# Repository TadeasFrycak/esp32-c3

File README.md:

# ESP32-C3 Nano

:warning: **Temporary warning**: This version of PCB has not been yet validated and it is actively being worked on

Compact and minimalist **ESP32-C3** breakout designed in [KiCAD](https://www.kicad.org/)

## Features
- **Breadboard friendly**
- **Compact dimensions** - 46 x 21.5 mm
- **USB-C** connector for programming (using CDC, so no external usb-serial convertor)
- **External VIN pin** with schottky diode (so both VIN and USB power can be applied at the same time)
- **Low dropout regulator to 3V3** (LDO)
- **Reset** and **Boot** buttons on board
- **Integrated PCB antenna**
- **USB ESD protection**
- Chip: **ESP32-C3FH4**

## Interactive HTML BOM
Thanks to the awesome KiCAD [IBOM](https://github.com/openscopeproject/InteractiveHtmlBom) plugin, we can now generate this stunning BOM! You can find it in docs/ibom.html

## Schematics

## Contributors:
- **SZKANDERA Filip** (filip.szkandera@gmail.com, [@FilipSzkandera](https://github.com/FilipSzkandera/))
- **FRYČÁK Tadeáš** (info@frycak.com, [@TadeasFrycak](https://github.com/TadeasFrycak/))

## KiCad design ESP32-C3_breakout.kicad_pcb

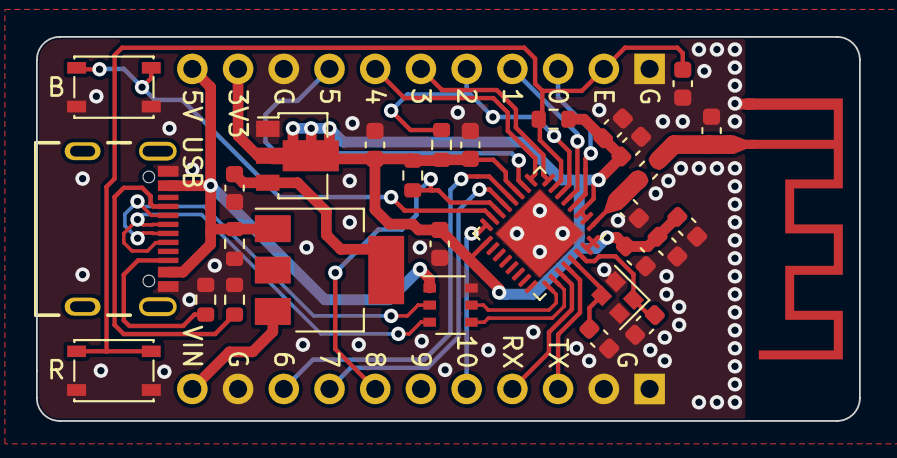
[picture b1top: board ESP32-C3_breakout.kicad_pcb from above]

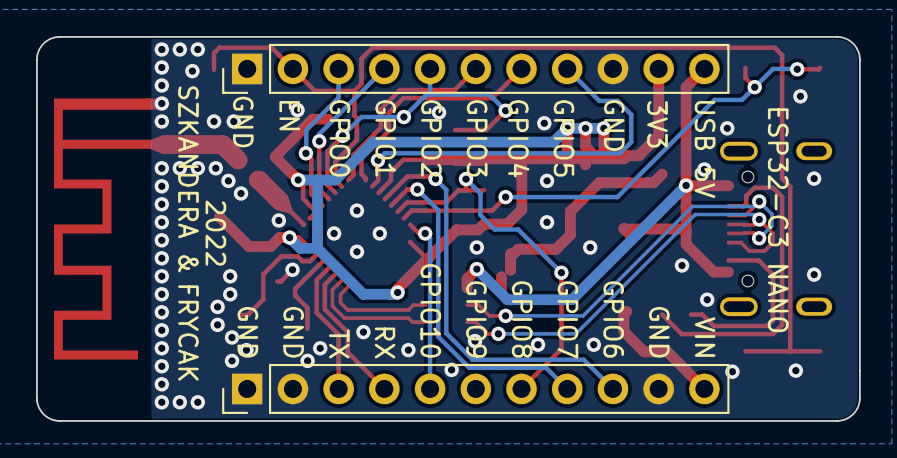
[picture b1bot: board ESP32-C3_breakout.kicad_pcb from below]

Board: 2 copper layers, 45.7 x 21.3 mm, 32 parts (2 on the bottom side), 29 nets.

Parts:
AE1: Antenna_Shield; ESPRESSIF_ESP32_MIFA_2.4GHz_Right
C1, C6, C10: 100n; C_0603_1608Metric
C2, C4, C9: 1u; C_0603_1608Metric
C3, C7, C8: 10u; C_0603_1608Metric
C11: 0.1u; C_0603_1608Metric
C12: 3.9 pF; C_0603_1608Metric
C13: 5.3pF; C_0603_1608Metric
C14, C15: 10p; C_0603_1608Metric
D1: BAT120C; SOT-223
IC1: STF202-22T1G; TSOP-6_1.65x3.05mm_P0.95mm
J1: USB4105-GF-A; GCT_USB4105-GF-A
J2, J3: Conn_01x11_Male; PinHeader_1x11_P2.54mm_Vertical
L1: 1.8 nH; L_0603_1608Metric
R1, R4, R5, R6: 10k; R_0603_1608Metric
R2, R3: 5k1; R_0603_1608Metric
SW1, SW2: SW_Push; SW_SPST_PTS810
U1: LD1117S33TR_SOT223; SOT-89-3
U2: ESP32-C3; QFN-32-1EP_5x5mm_P0.5mm_EP3.45x3.45mm
Y1: 40MHz; Crystal_SMD_2016-4Pin_2.0x1.6mm

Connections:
+3V3: C2.1, C3.1, C6.1, C7.1, C8.1, C9.1, C10.1, C11.1, J3.10, R1.1, R4.1, R5.1, U1.2 (VO), U2.2 (VDD3P3), U2.3 (VDD3P3), U2.11 (VDD3P3_RTC), U2.17 (VDD3P3_CPU), U2.31 (VDDA), U2.32 (VDDA)
/ANT: C13.1, L1.1, U2.1 (LNA_IN)
/BOOT: SW2.1, U2.15 (GPIO9/BOOT)
/D_N: IC1.2 (D(IN)_1), J1.A7 (DN1), J1.B7 (DN2)
/D_P: IC1.3 (D(IN)_2), J1.A6 (DP1), J1.B6 (DP2)
/EN: C4.1, J3.2, R1.2, SW1.1, U2.7 (CHIP_EN)
/GPIO0: J3.3, U2.4 (XTAL_32K_P/ADC1_CH0)
/GPIO1: J3.4, U2.5 (XTAL_32K_N/ADC1_CH1)
/GPIO2: J3.5, R4.2, U2.6 (GPIO2/ADC1_CH2)
/GPIO3: J3.6, U2.8 (GPIO3/ADC1_CH3)
/GPIO4: J3.7, U2.9 (MTMS/GPIO4/ADC1_CH4)
/GPIO5: J3.8, U2.10 (MTDI/GPIO5/ADC2_CH0)
/GPIO6: J2.9, U2.12 (MTCK/GPIO6)
/GPIO7: J2.8, U2.13 (MTDO/GPIO7)
/GPIO8: J2.7, R5.2, U2.14 (GPIO8)
/GPIO10: J2.5, U2.16 (GPIO10)
/RX: J2.4, U2.27 (U0RXD/GPIO20)
/TX: J2.3, U2.28 (U0TXD/GPIO21)
/USB_+5V: D1.1 (A1), IC1.1 (VBUS), J1.A4_B9 (VBUS), J1.B4_A9 (VBUS), J3.11, R6.1
/USB_D+: IC1.4 (D(OUT)_1), U2.26 (GPIO19/USB_D+)
/USB_D-: IC1.5 (D(OUT)_2), U2.25 (GPIO18/USB_D-)
/VIN: D1.3 (A2), J2.11
GND: AE1.2 (Shield), C1.2, C2.2, C3.2, C4.2, C6.2, C7.2, C8.2, C9.2, C10.2, C11.2, C12.2, C13.2, C14.2, C15.2, IC1.6 (GND), J1.A1_B12 (GND), J1.B1_A12 (GND), J2.1, J2.2, J2.10, J3.1, J3.9, R2.2, R3.2, R6.2, SW1.2, SW2.2, U1.1 (GND), U2.33 (GND), Y1.2, Y1.4
unnamed: AE1.1 (A), C12.1, L1.2
unnamed: C14.1, U2.29 (XTAL_N), Y1.3
unnamed: C15.1, U2.30 (XTAL_P), Y1.1
unnamed: J1.A5 (CC1), R2.1
unnamed: J1.B5 (CC2), R3.1
VDD: C1.1, D1.4 (K), U1.3 (VI)

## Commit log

2022-05-25 Added LDO
2022-05-25 Added USB-C
2022-05-25 General improvements
2022-05-26 Improved schematics
2022-05-29 Further improvements
2022-05-29 add: datasheets, distributors
2022-05-29 add: antenna π matching network values
    values, datasheets, distributors
2022-05-29 edit: ESP32C3FH4 distributor
2022-06-01 Differential pair routing change
2022-06-01 Minor improvements
2022-06-11 Power plane improvement
2022-06-27 edit: readme
2022-06-27 fix: readme
2022-08-21 Version 2
2022-08-24 Added interactive BOM
2022-08-24 Added IBOM
2022-08-24 Added ibom html reference
2022-08-25 Added schematic image
2025-05-25 update: README.md
